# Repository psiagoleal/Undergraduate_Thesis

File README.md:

# Automação de Interferômetro com Arduino (TCC)

Sistema de controle para um interferômetro de baixa coerência óptica (Michelson), desenvolvido em C++ para Arduino Nano e com hardware projetado em KiCAD. O sistema controla o movimento (passos) do espelho móvel com precisão, armazena posições na EEPROM e oferece interface por LCD/I2C ou via terminal serial.

Resumo do trabalho:
"DESENVOLVIMENTO DE UM SISTEMA DE CONTROLE DO INTERFERÔMETRO DE BAIXA COERÊNCIA PARA ESTUDOS DE ÍNDICE DE REFRAÇÃO EM MATERIAIS

Trabalho de Conclusão de Curso, apresentado à UEMS. Desenvolveu-se um sistema baseado em Arduino Nano para substituir o controle existente de um interferômetro de Michelson de baixa coerência (luz branca), utilizado para estudos de refração em materiais. O sistema controla o deslocamento do espelho móvel com precisão e permite configuração de parâmetros, armazenamento de posições e futura expansão com sensores/atuadores adicionais."

## Estrutura do repositório

- Hardware (KiCAD):
  - hardware/TCC.kicad_pcb, hardware/TCC.sch e arquivos auxiliares
  - hardware/Gerber/ (produção)
- Firmware (Arduino):
  - TCC8.0/src/main3.cpp — ponto de entrada do firmware
  - TCC8.0/lib — bibliotecas locais (LCD I2C, Soft I2C, Stepper, Interface, Config, etc.)
    - Interface gráfica no LCD: [`UserInterface::mainScreen`](TCC8.0/lib/Interface/Interface.cpp), telas como [`UserInterface::Screen30`](TCC8.0/lib/Interface/Interface.cpp), [`UserInterface::Screen40`](TCC8.0/lib/Interface/Interface.cpp), [`UserInterface::Screen50`](TCC8.0/lib/Interface/Interface.cpp), [`UserInterface::Screen510`](TCC8.0/lib/Interface/Interface.cpp)
    - Interface serial (modo terminal): [`InterfaceSerial::mainScreen`](TCC8.0/lib/InterfaceSerial/InterfaceSerial.cpp), telas 50x/51x/52x
    - Lógica de controle e variáveis globais: [`Data`](TCC8.0/lib/Config/Config.h) e seus getters/setters (ex.: [`Data::getScreenNumber`](TCC8.0/lib/Config/Config.cpp))
    - Driver de motor de passo: [`mStepper`](TCC8.0/lib/mStepper/mStepper.cpp)
    - Leitura de botões/sensores analógicos: [`Analog`](TCC8.0/lib/analogPins/analogPins.cpp), incluindo homing: [`Analog::trailSetup`](TCC8.0/lib/analogPins/analogPins.cpp)
    - Armazenamento em EEPROM (posições): exemplos em [`Select::BttnS312`](TCC8.0/lib/CommandsBttnS/CommandsBttnS.cpp)
- Aplicativos auxiliares de serial:
  - SerialComApp/ (exemplos C++ para comunicação via porta serial)
- Arquivos antigos e referências:
  - legacy/, refs/

## Funcionalidades principais

- Controle de motor de passo 4 fios, com passos por volta configurados (padrão: 64)
- Interface de usuário por LCD (I2C) com menu:
  - Zero Relativo (10x)
  - Ajuste Fino (30x)
  - Ajuste Grosso (40x)
  - Posições Salvas (50x/51x/52x), incluindo Zero Absoluto e posições 1–3
- Modo alternativo por terminal serial (9600 bps), com telas equivalentes (50x–52x)
- Persistência de posições em EEPROM (Zero Abs e posições 1–3)
- Rotina de homing pela leitura analógica (A1) para encontrar início de trilha: [`Analog::trailSetup`](TCC8.0/lib/analogPins/analogPins.cpp)

## Como compilar e gravar

1. Requisitos
   - Arduino Nano (ATmega328P)
   - IDE Arduino (1.8.x ou superior) ou Arduino CLI/PlatformIO
   - Baud rate: 9600 bps (Serial)

2. Passos
   - Abra a pasta TCC8.0 como projeto (o arquivo principal é [TCC8.0/src/main3.cpp](TCC8.0/src/main3.cpp), que define `setup()` e `loop()`).
   - Se usar IDE Arduino, coloque a pasta TCC8.0 como sketch. As bibliotecas usadas estão vendorizadas em TCC8.0/lib (LiquidCrystal_I2C, SoftI2C, etc.).
   - Selecione a placa “Arduino Nano” e a porta correta (ex.: COMx no Windows ou /dev/ttyACMx no Linux).
   - Compile e faça o upload.

Observações:
- A interface (LCD vs. terminal) é selecionada em tempo de execução a partir de [`Data::getSerialCom`](TCC8.0/lib/Config/Config.cpp), configurada em [`setup`](TCC8.0/src/main3.cpp) via `sc.SerialComSetup()` e constantes `SerialComNo`/`SerialComYes`.

## Uso

- Inicialização:
  - O firmware executa o homing com [`Analog::trailSetup`](TCC8.0/lib/analogPins/analogPins.cpp) para levar o espelho à referência da trilha.
  - Em seguida, abre a tela inicial via [`UserInterface::mainScreen`](TCC8.0/lib/Interface/Interface.cpp) ou [`InterfaceSerial::mainScreen`](TCC8.0/lib/InterfaceSerial/InterfaceSerial.cpp), conforme o modo.

- Controles (botões):
  - Códigos definidos em [TCC8.0/src/main3.cpp](TCC8.0/src/main3.cpp): RIGHT=0, UP=1, DOWN=2, LEFT=3, SELECT=4, CANCEL=5.
  - A navegação de telas é baseada em `ScreenNumber` (veja [`Data::getScreenNumber`](TCC8.0/lib/Config/Config.cpp)) e as telas `ScreenXX()` em Interface/InterfaceSerial.

- Salvamento/recuperação de posições:
  - Zero Absoluto é exibido em [`UserInterface::Screen510`](TCC8.0/lib/Interface/Interface.cpp) e equivalentes na interface serial.
  - Posições 1–3 têm telas de visualização e comandos de salvamento, com escrita na EEPROM (ex.: [`Select::BttnS312`](TCC8.0/lib/CommandsBttnS/CommandsBttnS.cpp)).

## Hardware

- Projeto da controladora e integrações no diretório [hardware/](hardware/)
  - Arquivos do KiCAD: TCC.sch, TCC.kicad_pcb, fabricáveis em [hardware/Gerber/](hardware/Gerber/)
- LCD I2C (PCF8574) com biblioteca local [`LiquidCrystal_I2C`](TCC8.0/lib/LiquidCrystal_I2C/LiquidCrystal_I2C.h) e suporte a Soft I2C

## Desenvolvimento

- Organização do código:
  - Lógica/estado: [`Data`](TCC8.0/lib/Config/Config.h, TCC8.0/lib/Config/Config.cpp)
  - UI LCD: [`UserInterface`](TCC8.0/lib/Interface/Interface.h, TCC8.0/lib/Interface/Interface.cpp)
  - UI Serial: [`InterfaceSerial`](TCC8.0/lib/InterfaceSerial/InterfaceSerial.h, TCC8.0/lib/InterfaceSerial/InterfaceSerial.cpp)
  - Controle motor: [`mStepper`](TCC8.0/lib/mStepper/mStepper.h, TCC8.0/lib/mStepper/mStepper.cpp)
  - Botões/sensores: [`Analog`](TCC8.0/lib/analogPins/analogPins.h, TCC8.0/lib/analogPins/analogPins.cpp)

- Parâmetros importantes:
  - Passos por volta: `stepsPerRevolution = 64` em [TCC8.0/lib/Variables/Variables.h](TCC8.0/lib/Variables/Variables.h)
  - Velocidades ajustáveis nas telas de configuração (20x), exibidas por [`UserInterface::Screen210`](TCC8.0/lib/Interface/Interface.cpp) e [`InterfaceSerial::Screen211`](TCC8.0/lib/InterfaceSerial/InterfaceSerial.cpp)
  - Salvamento de posições na EEPROM com endereços calculados em [TCC8.0/lib/Variables/Variables.h](TCC8.0/lib/Variables/Variables.h)

## SerialComApp

Exemplos C++ para comunicação serial com o Arduino estão em [SerialComApp/](SerialComApp/). Úteis para testes de leitura/escrita em Linux/Windows.

## 📄 Licença

MIT

## Contato

Projeto de TCC (Engenharia Física) — automação de interferômetro com Arduino. Para dúvidas técnicas, consulte os arquivos-fonte referenciados acima.

Link para monografia: https://drive.google.com/file/d/1YRrOQsxsX27IK1LEwe4l2IJH7da19-2-/view?usp=drive_link

---
## Apoie

**Feito com ❤️ por Iago Leal** | [☕ Apoie o criador]

Se este projeto ajudou você, considere apoiar:

- Buy Me a Coffee: https://buymeacoffee.com/psiagoleal

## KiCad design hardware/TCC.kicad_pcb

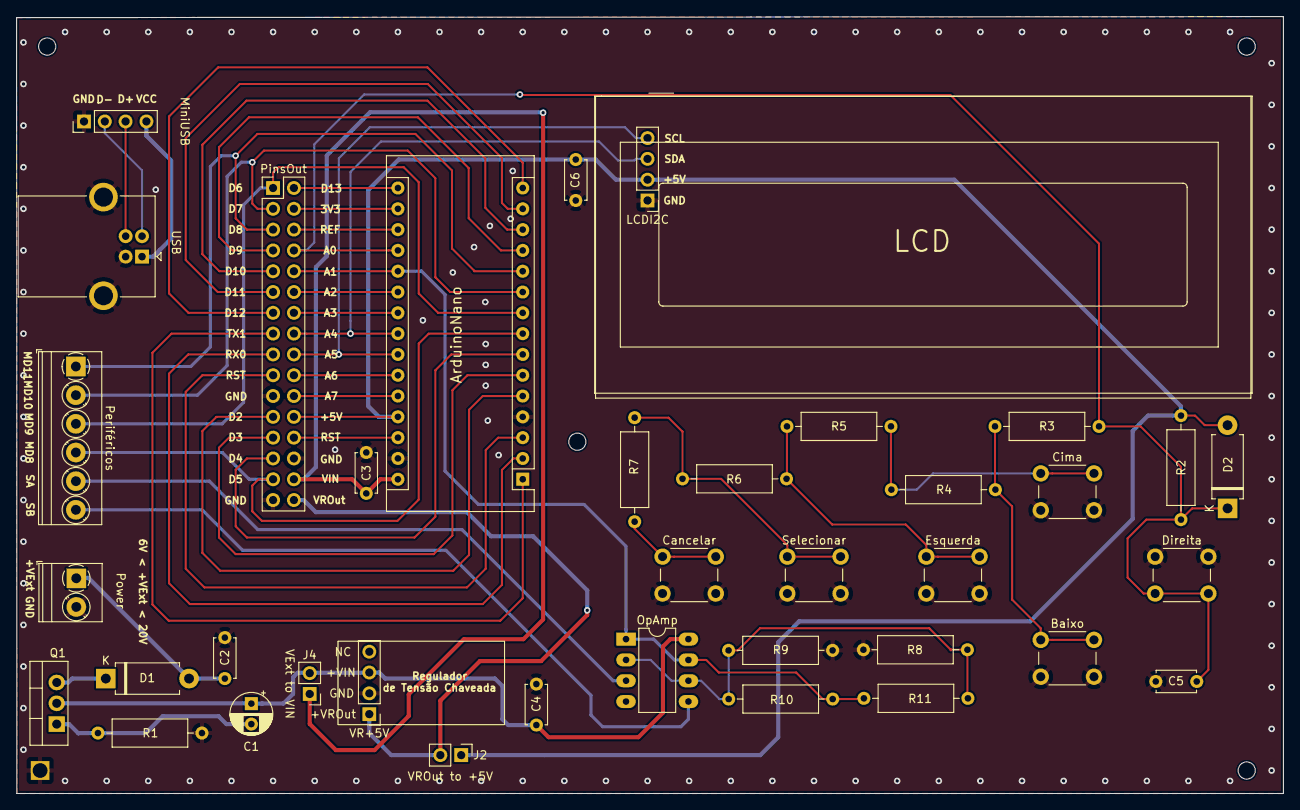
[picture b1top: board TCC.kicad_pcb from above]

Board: 2 copper layers, 154.7 x 94.9 mm, 42 parts (0 on the bottom side), 45 nets.

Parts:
ArduinoNano: Arduino_Nano_v3.x; Arduino_Nano
Baixo: SW_Push; SW_PUSH_6mm_H4.3mm
C1: 100uF; CP_Radial_D5.0mm_P2.50mm
C2, C3, C4, C5, C6: 100pF; C_Disc_D4.7mm_W2.5mm_P5.00mm
Cancelar: SW_Push; SW_PUSH_6mm_H4.3mm
Cima: SW_Push; SW_PUSH_6mm_H4.3mm
D1: SB360; D_DO-15_P10.16mm_Horizontal
D2: SB140; D_DO-15_P10.16mm_Horizontal
Direita: SW_Push; SW_PUSH_6mm_H4.3mm
Esquerda: SW_Push; SW_PUSH_6mm_H4.3mm
J2, J4: 22-23-2021; PinHeader_1x02_P2.54mm_Vertical
LCDI2C: 0022232041; PinHeader_1x04_P2.54mm_Vertical
MiniUSB: 0022232041; PinHeader_1x04_P2.54mm_Vertical
OpAmp: LM358; DIP-8_W7.62mm_LongPads
Periféricos: Screw_Terminal_01x06; TerminalBlock_Phoenix_PT-1,5-6-3.5-H_1x06_P3.50mm_Horizontal
PinsOut: Female_Header_16x02_2.54; PinHeader_2x16_P2.54mm_Vertical
Power: Screw_Terminal_01x02; TerminalBlock_Phoenix_PT-1,5-2-3.5-H_1x02_P3.50mm_Horizontal
Q1: IRF9Z24; TO-220-3_Vertical
R1: 1M; R_Axial_DIN0309_L9.0mm_D3.2mm_P12.70mm_Horizontal
R2: 3k9; R_Axial_DIN0309_L9.0mm_D3.2mm_P12.70mm_Horizontal
R3, R4, R5, R6, R7: 220; R_Axial_DIN0309_L9.0mm_D3.2mm_P12.70mm_Horizontal
R8, R9, R10, R11: R; R_Axial_DIN0309_L9.0mm_D3.2mm_P12.70mm_Horizontal
REF1, REF2, REF3, REF4, REF5: MountingHole_2.1mm
Selecionar: SW_Push; SW_PUSH_6mm_H4.3mm
USB: USB_B; USB_B_OST_USB-B1HSxx_Horizontal
VR+5V: 0022232041; PinHeader_1x04_P2.54mm_Vertical

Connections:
1: ArduinoNano.1, PinsOut.8
2: ArduinoNano.2, PinsOut.9
3: ArduinoNano.3, PinsOut.10
5: ArduinoNano.5, PinsOut.12
6: ArduinoNano.6, PinsOut.13
7: ArduinoNano.7, PinsOut.14
8: ArduinoNano.8, Periféricos.4, PinsOut.15
9: ArduinoNano.9, Periféricos.3, PinsOut.1
10: ArduinoNano.10, Periféricos.2, PinsOut.2
11: ArduinoNano.11, Periféricos.1, PinsOut.3
12: ArduinoNano.12, PinsOut.4
13: ArduinoNano.13, PinsOut.5
14: ArduinoNano.14, PinsOut.6
15: ArduinoNano.15, PinsOut.7
16: ArduinoNano.16, PinsOut.17
17: ArduinoNano.17, PinsOut.18
18: ArduinoNano.18, PinsOut.19
19: ArduinoNano.19, C5.1, D2.1, Direita.2, PinsOut.20, R2.2, R3.2
20: ArduinoNano.20, OpAmp.1, OpAmp.7, PinsOut.21, R10.1, R11.1
21: ArduinoNano.21, PinsOut.22
22: ArduinoNano.22, PinsOut.23
23: ArduinoNano.23, LCDI2C.3, PinsOut.24
24: ArduinoNano.24, LCDI2C.4, PinsOut.25
25: ArduinoNano.25, PinsOut.26
26: ArduinoNano.26, PinsOut.27
28: ArduinoNano.28, PinsOut.29
29: ArduinoNano.4, ArduinoNano.29, Baixo.2, C2.2, C3.2, C4.2, C5.2, C6.1, Cancelar.2, Cima.2, Direita.1, Esquerda.2, LCDI2C.1, MiniUSB.1, PinsOut.11, PinsOut.16, PinsOut.30, Power.2, R1.2, R8.2, R9.2, REF4.1, Selecionar.2, USB.4, USB.5, VR+5V.2
30: ArduinoNano.30, C3.1, J4.1, PinsOut.31
+5V: ArduinoNano.27, C6.2, D2.2, J2.1, LCDI2C.2, PinsOut.28, R2.1
+VIN: C1.1, C4.1, J4.2, OpAmp.8, Q1.2, VR+5V.3
+VOUT: J2.2, PinsOut.32, VR+5V.1
unnamed: Baixo.1, R3.1, R4.1
unnamed: C1.2, Q1.1, R1.1
unnamed: Cancelar.1, R7.2
unnamed: Cima.1, R4.2, R5.1
unnamed: D1.1, Q1.3
unnamed: Esquerda.1, R5.2, R6.1
unnamed: MiniUSB.2, USB.2
unnamed: MiniUSB.3, USB.3
unnamed: MiniUSB.4, USB.1
unnamed: OpAmp.2, OpAmp.6, R8.1, R9.1, R10.2, R11.2
unnamed: R6.2, R7.1, Selecionar.1
SA: OpAmp.3, Periféricos.5
SB: OpAmp.5, Periféricos.6
VCC: C2.1, D1.2, Power.1

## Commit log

2025-10-31 Track CAD/3D with Git LFS
2025-10-31 Atualizando com hardware e tentando organizar
